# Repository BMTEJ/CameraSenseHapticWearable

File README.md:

# CameraSenseHapticWearable

A wearable custom PCB with mounted camera, ESP32 Wroom2, haptic feedback, and 3v8 rechargeable battery to sense when wearer is leaving bounds of crosswalk.
If they exiting left, two vibrations, if right, one vibration.

Components:
ESP32-S3-Wroom2
LRA
LRA driver
ArduCam
3V8 LiPo

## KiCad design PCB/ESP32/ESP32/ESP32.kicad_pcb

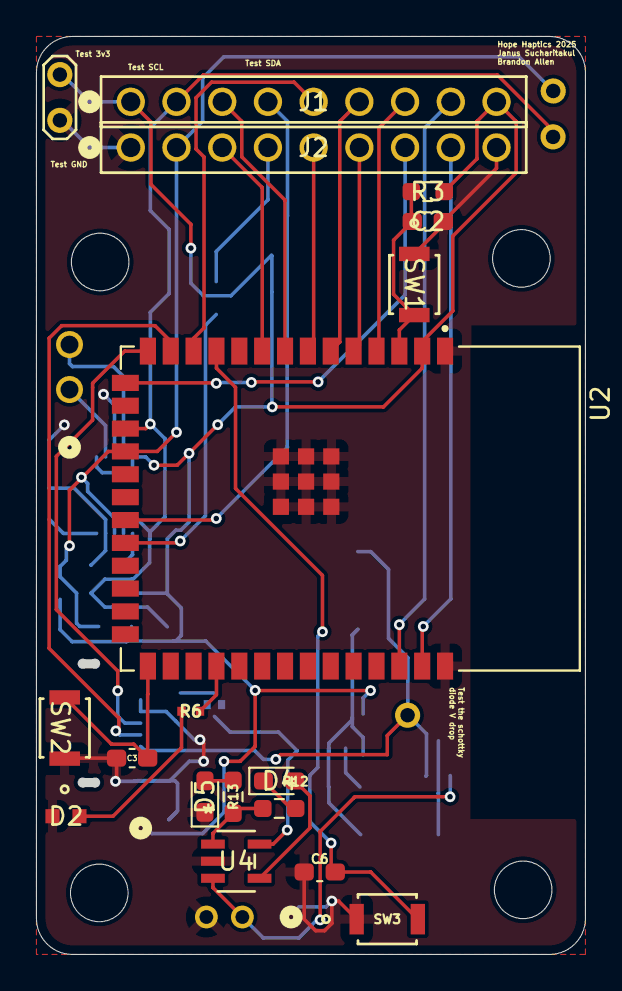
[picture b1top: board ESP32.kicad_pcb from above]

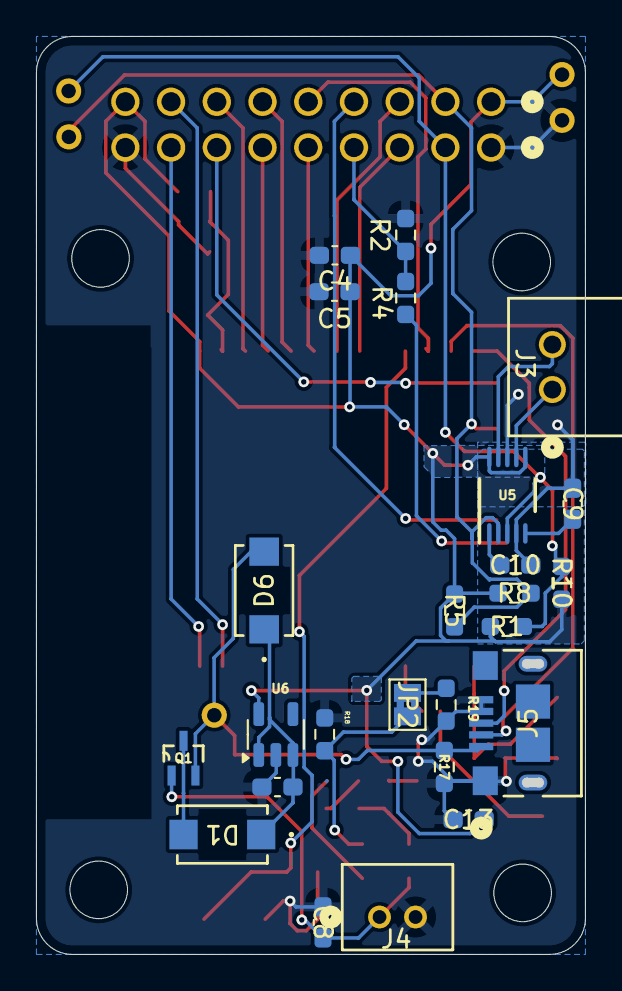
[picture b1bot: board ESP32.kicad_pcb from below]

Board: 2 copper layers, 30.0 x 50.5 mm, 42 parts (25 on the bottom side), 37 nets.

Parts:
C2, C3, C4, C6, C10: .1uF; C_0603_1608Metric_Pad1.08x0.95mm_HandSolder
C5, C9, C12, C13: 1uF; C_0603_1608Metric_Pad1.08x0.95mm_HandSolder
C8: 10μF; C_0603_1608Metric_Pad1.08x0.95mm_HandSolder
D1, D6: D_Schottky; CR_SMA_403AE_OSI-L
D2: LED; LEDIndicator
D4, D5: LED; D_0603_1608Metric_Pad1.05x0.95mm_HandSolder
J1, J2: PPTC091LFBN-RC; CONN9_PPTC091LFBN-RC_SUL
J3: Conn_01x02_Pin; CONN_S2B-XH-A_JST
J4: Conn_01x02_Socket; CONN2_B2B-PH-K-S_JST
J5: USB_B_Micro; CONN_10118193-0001LF_AMP
JP2: SolderJumper_2_Open; SolderJumper-2_P1.3mm_Bridged2Bar_Pad1.0x1.5mm
Q1: PMOS; SOT65P210X110-3N
R1, R3, R5, R17: 10k; R_0603_1608Metric_Pad0.98x0.95mm_HandSolder
R2, R4: 4.7k; R_0603_1608Metric_Pad0.98x0.95mm_HandSolder
R6: 160hm; RESIndicatpr
R8, R10: 2.2k; R_0603_1608Metric_Pad0.98x0.95mm_HandSolder
R12, R13: 330 ohm; R_0603_1608Metric_Pad0.98x0.95mm_HandSolder
R18: 10K; R_0603_1608Metric_Pad0.98x0.95mm_HandSolder
R19: 2.5K; R_0603_1608Metric_Pad0.98x0.95mm_HandSolder
SW1: RESET; B3U-1000P
SW2: BOOT; B3U-1000P
SW3: LRA Switch; B3U-1000P
U2: ESP32-S2-SOLO-U-N4; XCVR_ESP32-S2-SOLO-N4
U4: MCP73832T-2ACI/OT; SOT-23-5_MC_MCH
U5: DRV2605LTDGSRQ1; DGS0010A_L
U6: AP2112K-3.3; SOT-23-5

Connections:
+3V3: C4.1, C5.1, C13.1, J1.1, J1.9, R1.1, R3.1, R5.1, R8.1, R10.1, U2.2 (3V3), U5.6 (VDD_NC), U5.10 (VDD), U6.5 (VOUT)
/D0: J2.8, U2.39 (IO1)
/D1: J1.8, U2.38 (IO2)
/D2: J2.7, U2.15 (IO3)
/D3: J1.7, U2.4 (IO4)
/D4: J2.6, U2.5 (IO5)
/D5: J1.6, U2.6 (IO6)
/D6: J2.5, U2.7 (IO7)
/D7: J1.5, U2.12 (IO8)
/HS: J2.3, U2.9 (IO16)
/MCLK: R4.1, U2.22 (IO14)
/PCLK: J1.4, U2.21 (IO13)
/SCL: J1.2, R5.2, R8.2, U2.17 (IO9), U5.2 (SCL)
/SDA: J2.2, R1.2, R10.2, U2.18 (IO10), U5.3 (SDA)
/USB_D+: J5.3 (D+), U2.14 (IO20)
/USB_D-: J5.2 (D-), U2.13 (IO19)
/VS: J1.3, U2.8 (IO15)
GND: C2.1, C3.1, C4.2, C5.2, C6.1, C8.2, C9.1, C10.2, C12.1, C13.2, D2.1 (K), D5.1 (K), J2.1, J2.9, J4.2, J5.4 (ID), J5.5 (GND), J5.6 (Shield), R2.2, R17.2, R18.2, R19.1, SW1.1 (A), SW2.1 (A), SW3.1 (A), U2.1 (GND), U2.40 (GND__1), U2.41_1 (EPAD), U2.41_2 (EPAD__1), U2.41_3 (EPAD__2), U2.41_4 (EPAD__3), U2.41_5 (EPAD__4), U2.41_6 (EPAD__5), U2.41_7 (EPAD__6), U2.41_8 (EPAD__7), U2.41_9 (EPAD__8), U4.2, U5.4 (IN_TRIG), U5.8 (GND), U6.2 (GND)
unnamed: D1.2 (A), Q1.3 (S)
unnamed: C12.2, D1.1 (K), D6.1 (K), U6.1 (VIN), U6.3 (EN)
unnamed: D2.2 (A), R6.2
unnamed: D4.2 (A), D6.2 (A), J5.1 (VBUS), Q1.2 (G), R17.1, U4.4
unnamed: D4.1 (K), R12.1
unnamed: D5.2 (A), R13.1
unnamed: J2.4, R2.1, R4.2
unnamed: J3.1, U5.7 (OUT+)
unnamed: J3.2, U5.9 (OUT-)
unnamed: C8.1, J4.1, Q1.1 (D), U4.3
unnamed: JP2.1 (A), R19.2
unnamed: JP2.2 (B), R18.1, U4.5
unnamed: R12.2, R13.2, U4.1
unnamed: C2.2, R3.2, SW1.2 (B), U2.3 (EN)
unnamed: C3.2, SW2.2 (B), U2.27 (IO0)
unnamed: C6.2, SW3.2 (B), U2.11 (IO18)
unnamed: R6.1, U2.30 (IO37)
unnamed: C9.2, U5.5 (EN)
unnamed: C10.1, U5.1 (REG)

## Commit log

2025-03-16 BatterySchematic
2025-03-16 LRA schematic done for now. Will add button to activate LRA to demonstrate use later.
2025-03-16 Finalized recharge circuit
2025-03-20 ESP32 S2 schematic done.
2025-04-03 Create Final Schematic
2025-04-03 Create ChristianSchematic
2025-04-03 not sure what this stuff is.
2025-04-03 done.
2025-04-03 Coworking test
2025-04-03 test
2025-04-03 test.
2025-04-03 Prelim footprints
2025-04-03 Footprints for battery
2025-04-03 Schottky Diode footprint
2025-04-03 changes
    Changes?
2025-04-03 Footprint ad
    Switches footprints and JST footprints
2025-04-03 Footprints finished
    Finished JST, LRA footprint assignment
2025-04-03 Updated footprints for imported circuits
    done
2025-04-03 jhgj
2025-04-03 Updated resistor values
2025-04-03 Layout
2025-04-03 Updated camera
2025-04-04 Charging schematic done
2025-04-04 ddasd
    as
2025-04-04 sda
    dsada
2025-04-04 das
    dasdas
2025-04-04 New and improved footprint. Started layout
2025-04-04 dsa
    dsda
2025-04-04 ERC checkoff
2025-04-06 Entire layout done. DRC can go-. May need to ask about edge cut errors
2025-04-07 Fixes
    Fixed 3v3 net, added labels for different bus voltages, cleaned up silkscreen.
2025-04-10 WIP of the new layout.
2025-04-12 Full final layout. A little over 2sq Inches
